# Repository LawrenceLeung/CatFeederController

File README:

Cat feeder control board w ATTINY

Designed for single layer etch process

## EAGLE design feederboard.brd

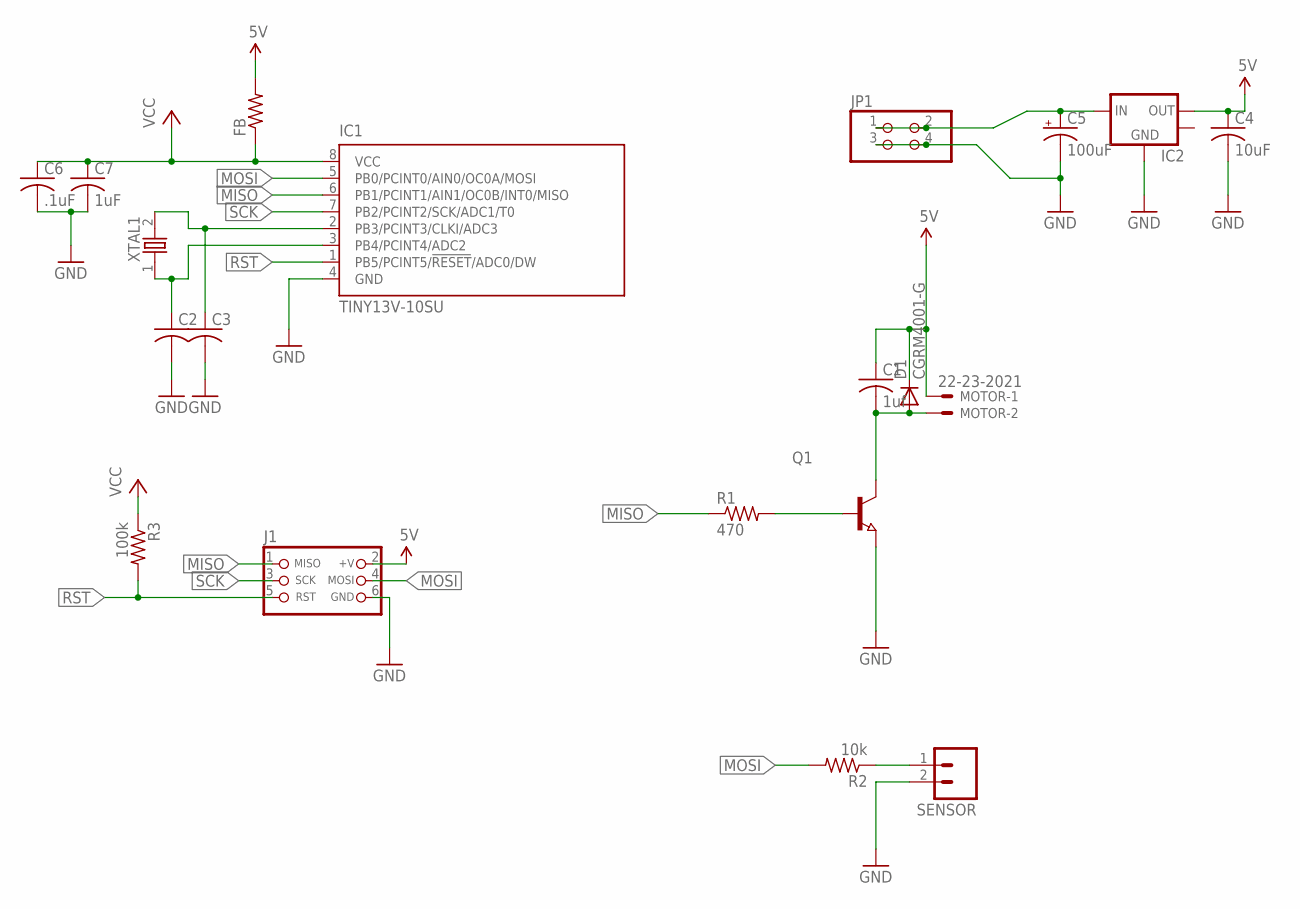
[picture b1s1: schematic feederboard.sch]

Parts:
C1: 1uf; C0805K
C2, C3: C-USC0805; C0805
C4: 10uF; C0805K
C5: 100uF; PANASONIC_C
C6: .1uF; C0603
C7: 1uF; C0603
D1: CGRM4001-G; SOD-123_MINI-SMA
FB: R-US_R0805; R0805
IC1: TINY13V-10SU; 8S2
IC2: V_REG_LM1117SOT223; SOT223
J1: CON_HEADER_PRG_AVR_ICSP_ETCH; HEADER_PRG_2X03_ETCH
JP1: PINHD-2X2/90; 2X02/90
MOTOR: 22-23-2021
Q1: NPN-TRANSISTOR_SOT23; SOT23
R1: 470; R0805
R2: 10k; R0805
R3: 100k; R0805
SENSOR: M02JST-PTH-2; JST-2-PTH
XTAL1: OSC-XTAL; HC-49U-OR-DIP

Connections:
5V: C1.1, C4.1, D1.C, FB.2, IC2.2 (VR-OUTSM), J1.2 (+V), MOTOR.1
GND: C2.2, C3.2, C4.2, C5.-, C6.2, C7.2, IC1.4 (GND), IC2.1 (GND), J1.6 (GND), JP1.3, JP1.4, Q1.2 (E), SENSOR.2
MISO: IC1.6 (PB1/PCINT1/AIN1/OC0B/INT0/MISO), J1.1 (MISO), R1.1
MOSI: IC1.5 (PB0/PCINT0/AIN0/OC0A/MOSI), J1.4 (MOSI), R2.2
unnamed: C2.1, IC1.3 (PB4/PCINT4/ADC2), XTAL1.1
unnamed: C3.1, IC1.2 (PB3/PCINT3/CLKI/ADC3), XTAL1.2
unnamed: C1.2, D1.A, MOTOR.2, Q1.3 (C)
unnamed: Q1.1 (B), R1.2
RST: IC1.1 (PB5/PCINT5/!RESET!/ADC0/DW), J1.5 (RST), R3.2
SCK: IC1.7 (PB2/PCINT2/SCK/ADC1/T0), J1.3 (SCK)
SWITCH: R2.1, SENSOR.1
VCC: C6.1, C7.1, FB.1, IC1.8 (VCC), R3.1
VIN: C5.+, IC2.3 (IN), JP1.1, JP1.2

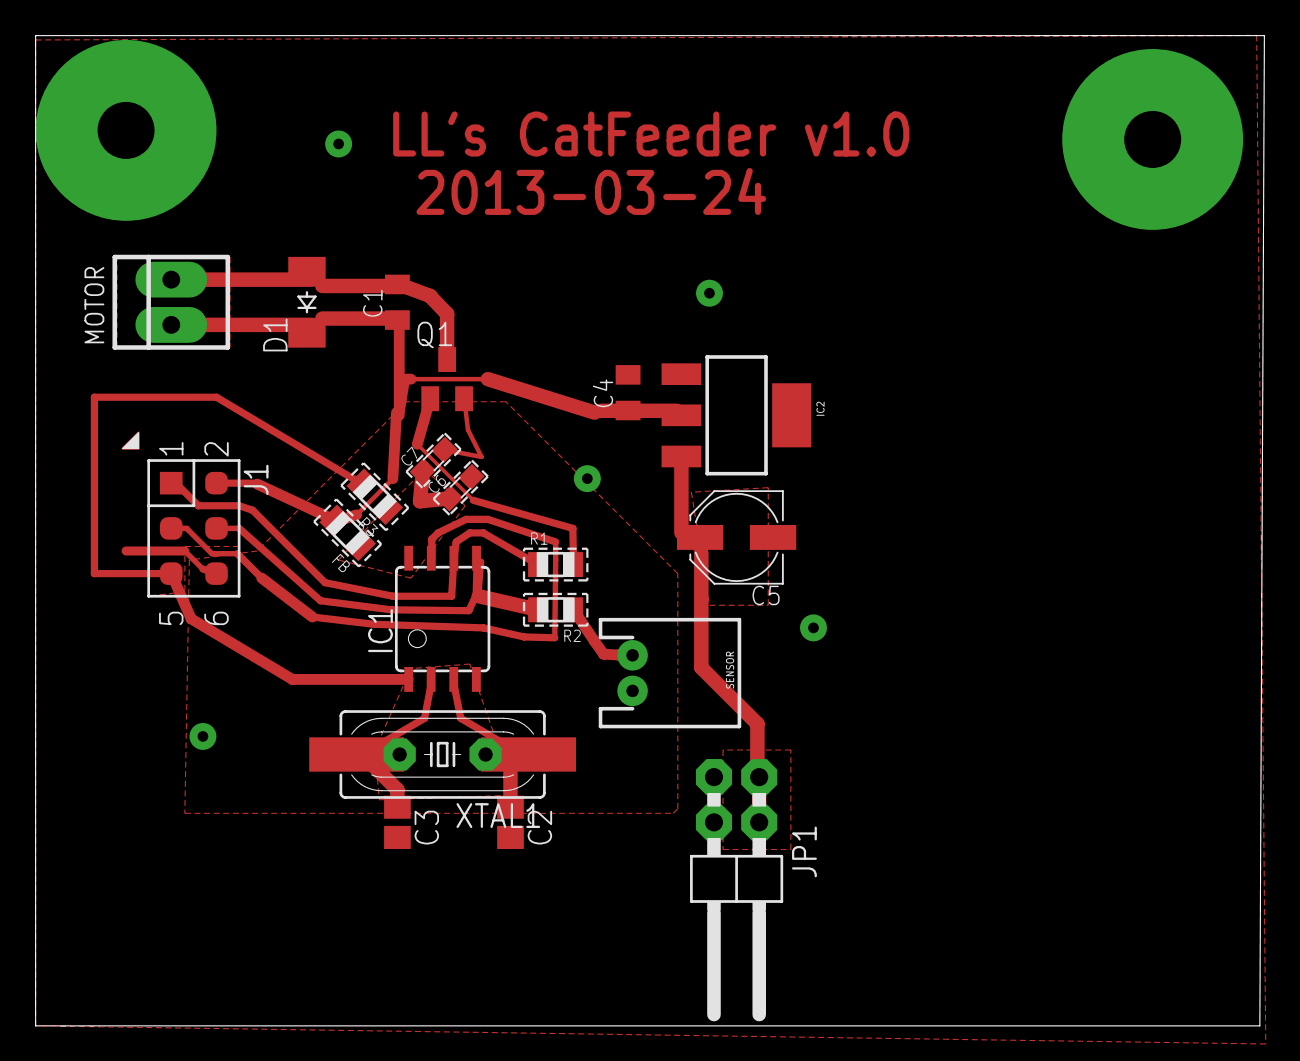
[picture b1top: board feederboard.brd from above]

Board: 2 copper layers, 69.0 x 55.6 mm, 20 parts (0 on the bottom side), 13 nets.

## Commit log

2013-02-26 Import into git
2013-03-11 Pullup for reset
2013-03-24 Add silk for printing
2013-03-31 Add PTC fuse on 5V rail
2013-04-27 Feeder testing arduino code
2013-05-11 Updated tester and new Timer code

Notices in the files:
parts and their libraries:
SparkFun-Connectors: Licensing: CC v3.0 Share-Alike You are welcome to use this library for commercial purposes.
